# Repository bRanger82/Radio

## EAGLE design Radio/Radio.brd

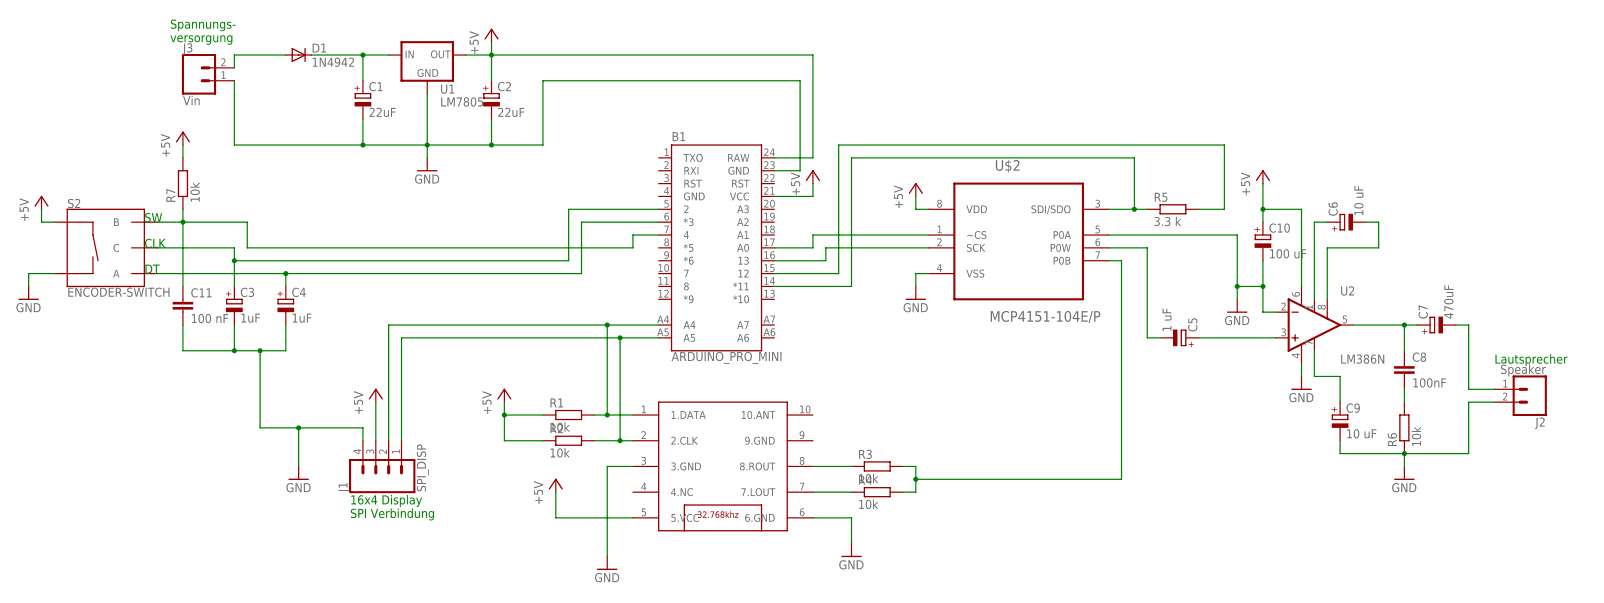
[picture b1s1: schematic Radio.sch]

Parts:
B1: ARDUINO_PRO_MINI
C1, C2: 22uF; E2,5-6E
C3, C4: 1uF; E5-10,5
C5: 1 uF; E5-10,5
C6, C9: 10 uF; E5-10,5
C7: 470uF; E5-10,5
C8: 100nF; C025-040X050
C10: 100 uF; E5-10,5
C11: 100 nF; C025-040X050
D1: 1N4942; DO41-10
J1: SPI_DISP; 1X04
J2: Speaker; 1X02
J3: Vin; 1X02
R1, R2, R3, R4, R6, R7: 10k; 0207/10
R5: 3.3 k; 0207/10
S2: ENCODER-SWITCH; ROTARY_ENC_PLAIN
U1: LM7805; 78XXL
U2: LM386N; DIP08
U$1: TEA5767; TJ-102BC
U$2: MCP4151-104E/P; DIP254P762X533-8

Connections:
+5V: B1.21 (VCC), B1.24 (RAW), C2.+, C10.+, J1.3, R1.1, R2.1, R7.2, S2.SW+, U1.OUT, U2.6 (V+), U$1.5 (5.VCC), U$2.8 (VDD)
GND: B1.4 (GND), B1.23 (GND), C1.-, C2.-, C3.-, C4.-, C9.-, C10.-, C11.2, J1.4, J2.2, J3.1, R6.1, S2.SW-, U1.GND, U2.2 (-IN), U2.4 (V-), U$1.3 (3.GND), U$1.6 (6.GND), U$2.4 (VSS), U$2.5 (P0A)
unnamed: C1.+, D1.C, U1.IN
unnamed: B1.A4, J1.2, R1.2, U$1.1 (1.DATA)
unnamed: B1.A5, J1.1, R2.2, U$1.2 (2.CLK)
unnamed: B1.7 (4), C11.1, R7.1, S2.B
unnamed: R3.1, U$1.8 (8.ROUT)
unnamed: R4.1, U$1.7 (7.LOUT)
unnamed: R3.2, R4.2, U$2.7 (P0B)
unnamed: C8.2, R6.2
unnamed: B1.14 (*11), R5.1, U$2.3 (SDI/SDO)
unnamed: B1.17 (A0), U$2.1 (~CS)
unnamed: B1.16 (13), U$2.2 (SCK)
unnamed: B1.15 (12), R5.2
unnamed: C5.-, U$2.6 (P0W)
unnamed: C5.+, U2.3 (+IN)
unnamed: C6.+, U2.1 (GAIN)
unnamed: C6.-, U2.8 (GAIN)
unnamed: C7.+, C8.1, U2.5 (OUT)
unnamed: D1.A, J3.2
unnamed: C9.+, U2.7 (BP)
unnamed: B1.5 (2), C3.+, S2.C
unnamed: B1.6 (*3), C4.+, S2.A
unnamed: C7.-, J2.1

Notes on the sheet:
Lautsprecher
Spannungs- versorgung
16x4 Display SPI Verbindung
CLK

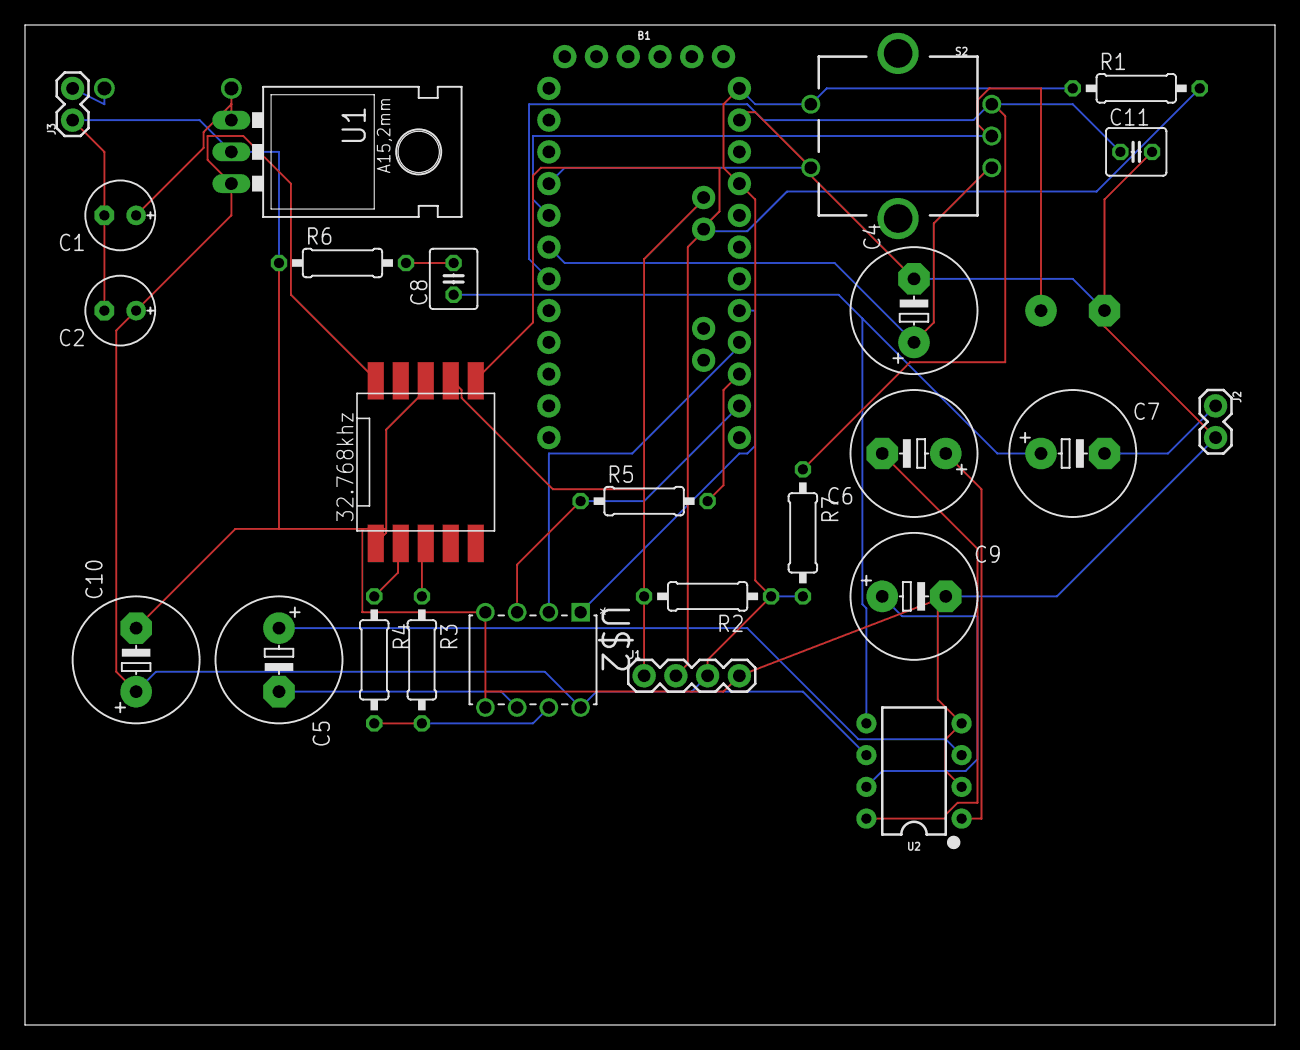
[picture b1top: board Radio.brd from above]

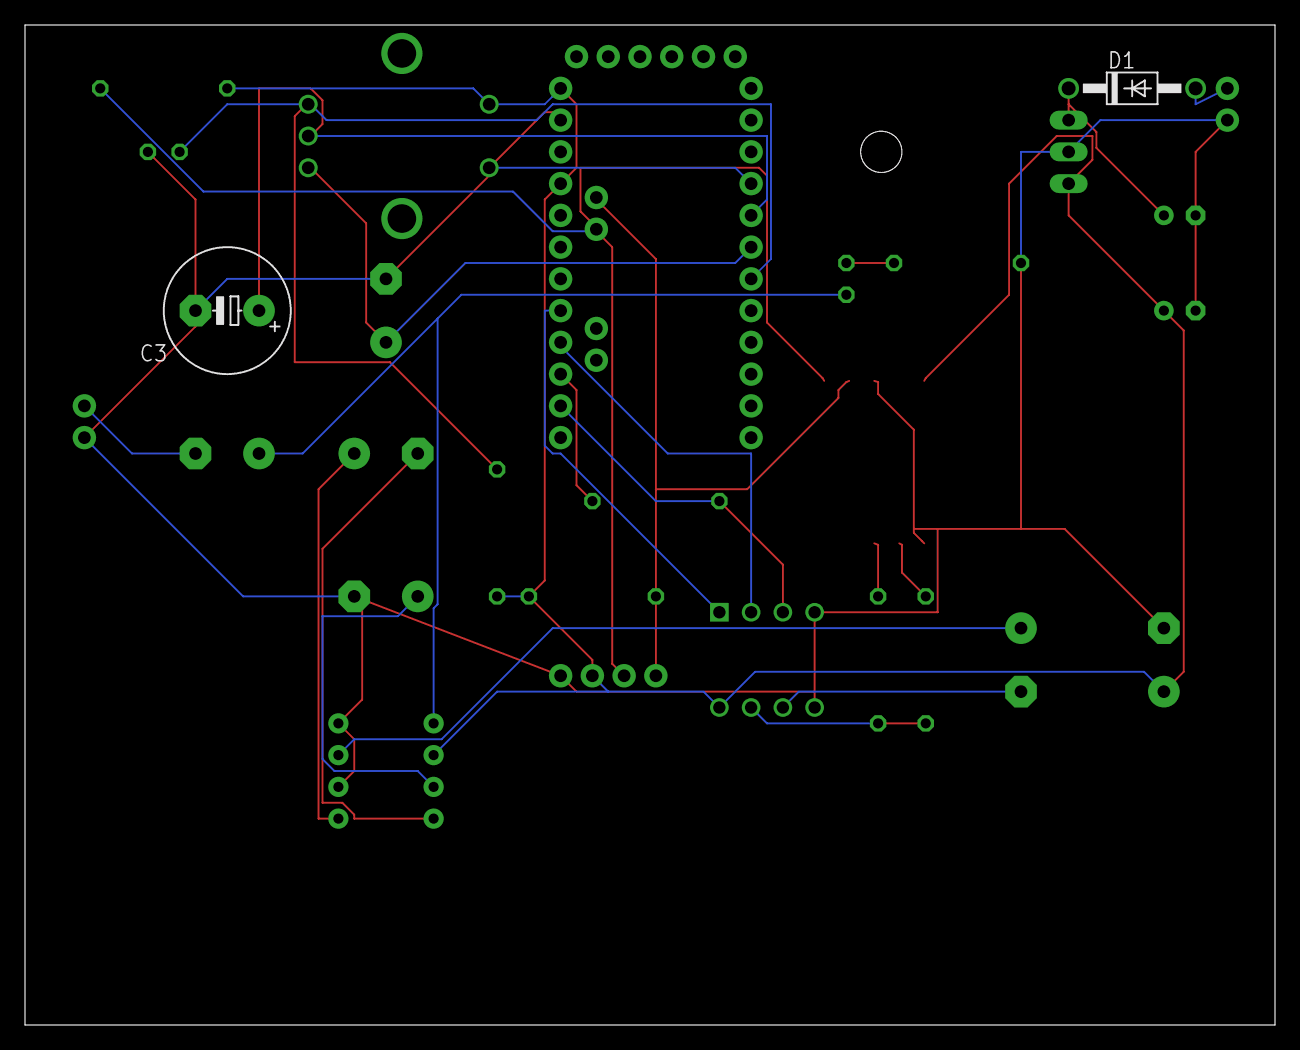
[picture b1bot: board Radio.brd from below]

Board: 2 copper layers, 100.0 x 80.0 mm, 28 parts (2 on the bottom side), 24 nets.

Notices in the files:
parts and their libraries:
SparkFun-Boards: Licensing: Creative Commons ShareAlike 4.0 International - https://creativecommons.org/licenses/by-sa/4.0
